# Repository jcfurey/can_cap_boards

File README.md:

# can_cap_boards

A repo to contain different PCBs with associated gerber files and SPICE sim docs.

The theme: small interior-mount boards that retire vintage multi-section
twist-lock "can" electrolytics in tube amps, replacing them with discrete,
individually serviceable modern radial caps.

> ⚠️ These boards carry **lethal B+ voltages** (400 V+). Discharge and meter
> every section to zero before handling. See each board's README.

## Boards

| Board | Amp | What it replaces | Status |
|-------|-----|------------------|--------|
| [`princeton_reverb_aa1164`](princeton_reverb_aa1164/) | Fender Princeton Reverb (AA1164) | 4-section can → 47/22/22/33 µF | design + BOM + SPICE + KiCad project (DRC-clean starter) + gerbers |

Each board folder contains its own `README.md` (design notes), `BOM.md`, an
illustrated `design_reference.html` (schematic + mechanical drawings), a `sim/`
directory with the SPICE supply model, and a `kicad/` directory with the KiCad
sources and `kicad/fab/` fabrication outputs (gerbers, drill, BOM, position).

## License

Apache-2.0 (see [`LICENSE`](LICENSE)).

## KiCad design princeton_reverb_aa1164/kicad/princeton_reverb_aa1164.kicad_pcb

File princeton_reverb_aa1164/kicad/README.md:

# KiCad project — AA1164 Filter Cap Board

KiCad 7 project for the Princeton Reverb (AA1164) filter-cap board. This is a
**starting point**: electrically complete, ERC/DRC-clean, with the HV creepage
and split-ground rules baked in — but the placement and mechanical fit still
want a pass in the GUI before you fab it.

> Built/validated with KiCad **7.0.11**. KiCad 9 opens it fine (it will offer to
> upgrade the files). The two generator scripts below are the scaffolding used
> to create it; the `.kicad_sch` / `.kicad_pcb` are now the editable sources.

*B.Cu split ground pours (blue) joined only at the NT1 star-tie; F.Cu B+ traces
(red); 2×2 caps with each B+ wire-entry beside its cap; bleeder R1/R2 top-left;
mounting holes right. The wide white rings are the 2.5 mm HV anti-pads in the
pour.*

## Files

| File | What |
|------|------|
| `princeton_reverb_aa1164.kicad_pro` | Project (net classes: 2.5 mm clearance / 2.5 mm tracks) |
| `princeton_reverb_aa1164.kicad_sch` | Schematic — 4 caps, bleeder, 6 wire-entry pads, star-tie, 2 mounts |
| `princeton_reverb_aa1164.kicad_pcb` | 2-layer board: B+ on F.Cu, split GND pours on B.Cu |
| `wire_entry.pretty/` | Custom footprints: `WireEntry_BPlus`, `WireEntry_GND` (1.6 mm hole / 3.3 mm pad), `StarTie_8mm` (net-tie) |
| `fp-lib-table` / `sym-lib-table` | Register the project footprint library |
| `generate_sch.py` / `generate_pcb.py` | The scripts that generated the above (kiutils + pcbnew) |
| `fab/` | Fabrication outputs — see `fab/` |
| `drc.rpt` | Saved DRC run (0 errors) |

## Nets & rules

- B+ nodes are **separate nets** `HV_A..HV_D` (each = wire-entry pad + cap "+",
  plus the bleeder on A) — they only join *outside* the board, in the amp.
- `BLEED_MID` is the junction of the two series bleeder resistors.
- Grounds are **two nets** `GND-PWR` (caps A·B + bleeder) and `GND-PRE`
  (caps C·D), joined **only** at the `NT1` star-tie (a net-tie footprint, so DRC
  permits the single intentional short). Omit/DNP NT1 to run dual returns.
- Board-wide clearance is **2.5 mm** and default track width **2.5 mm** — every
  net here is HV or ground, so one rule enforces the creepage spec everywhere.

## Validation

- **Connectivity** verified by netlist export (matches the intended net map).
- **DRC: 0 errors.** The 12 remaining items are warnings only:
  - `lib_footprint_issues` (8) — headless DRC has no global footprint-library
    table; these disappear in the GUI.
  - `silk_over_copper` (4) — cosmetic cap-outline silk over mask openings.
- KiCad 7's `kicad-cli` has no `erc`/`drc` subcommand (KiCad 8+), so ERC/DRC were
  run via the netlist export and `pcbnew.WriteDRCReport`. **Re-run ERC and DRC in
  your GUI** as a final check after any edits.

## Refine before fabbing

This was placed/routed *blind to the real chassis*. In the GUI:

1. **Verify mechanical fit** — board outline (~60 × 54 mm here vs the ~55–60 × 48
   target), the wire-entry positions against your fiber board, and cap body
   height clearance into the interior.
2. Optionally **regroup the wire-entry pads into one edge row** (they're placed
   next to each cap here for short, clean B+ traces).
3. Confirm the **cap footprints** — all four use `CP_Radial_D16.0mm_P7.50mm`
   (sized for the 47 µF); the 22/33 µF bodies are smaller, so swap to the right
   case once you pick exact parts.
4. Confirm the **bleeder** uses a vertical 2 W footprint that matches your
   resistors, and that the **star-tie** location suits your single chassis tie.
5. Re-run ERC + DRC.

## Regenerating

```sh
pip install kiutils
python3 generate_sch.py      # writes the .kicad_sch
python3 generate_pcb.py      # writes the .kicad_pcb, fills zones, runs DRC
```
Regenerating overwrites GUI edits — once you start editing in KiCad, treat the
`.kicad_sch`/`.kicad_pcb` as the sources and retire the scripts.

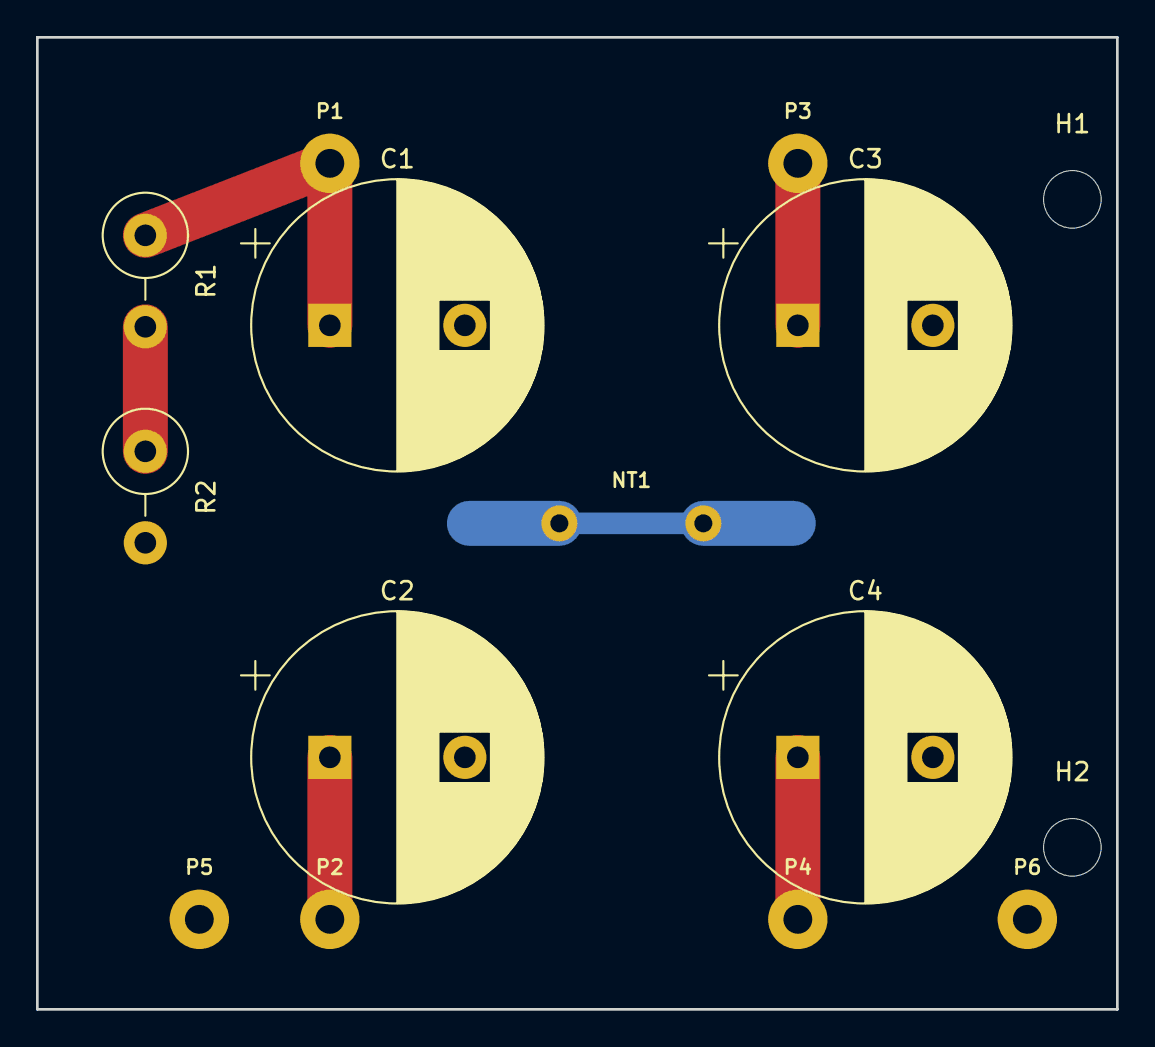
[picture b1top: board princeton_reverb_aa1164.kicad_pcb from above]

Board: 2 copper layers, 60.0 x 54.0 mm, 15 parts (0 on the bottom side), 7 nets.

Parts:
C1: 47uF; CP_Radial_D16.0mm_P7.50mm
C2, C3: 22uF; CP_Radial_D16.0mm_P7.50mm
C4: 33uF; CP_Radial_D16.0mm_P7.50mm
H1, H2: MountingHole_3.2mm_M3
NT1: STAR; StarTie_8mm
P1: B+1_A; WireEntry_BPlus
P2: B+2_B; WireEntry_BPlus
P3: B+3_C; WireEntry_BPlus
P4: B+4_D; WireEntry_BPlus
P5: GND-PWR; WireEntry_GND
P6: GND-PRE; WireEntry_GND
R1, R2: 100k; R_Axial_DIN0414_L11.9mm_D4.5mm_P5.08mm_Vertical

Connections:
BLEED_MID: R1.2, R2.1
GND-PRE: C3.2, C4.2, NT1.2, P6.1
GND-PWR: C1.2, C2.2, NT1.1, P5.1, R2.2
HV_A: C1.1, P1.1, R1.1
HV_B: C2.1, P2.1
HV_C: C3.1, P3.1
HV_D: C4.1, P4.1

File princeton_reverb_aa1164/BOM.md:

# BOM — Princeton Reverb (AA1164) Filter Cap Board

Rev F electrical design. Quantities are **per board**.

> **Scope:** only the parts that live *on this board* — the four filter caps,
> the bleeder, and the ground star link. The dropping resistors (1 k / 4.7 k /
> 10 k) between nodes stay on the amp's eyelet board and are **not** part of this
> BOM; they appear in the SPICE model (`sim/`) only to reproduce the node
> voltages.

## Filter capacitors

All electrolytics: aluminium, radial, **≥ 500 V**, **105 °C**, 7.5 mm pitch.
Anchor family: **Nichicon UCY** (voltage code `2H` = 500 V, `M` = ±20 %).
Confirm the exact case-size suffix at the distributor — it varies with µF.

| Ref | Node | Value | Rating | Suggested P/N | Qty |
|-----|------|------:|--------|---------------|:---:|
| C1 | A — B+1 reservoir / 6V6 plates | 47 µF | 500 V 105 °C | Nichicon UCY2H470MHD (16 × 40 mm) | 1 |
| C2 | B — B+2 screens | 22 µF | 500 V 105 °C | Nichicon UCY2H220M&lt;suffix&gt; | 1 |
| C3 | C — B+3 PI / reverb driver | 22 µF | 500 V 105 °C | Nichicon UCY2H220M&lt;suffix&gt; | 1 |
| C4 | D — B+4 preamp / reverb recovery | 33 µF | 500 V 105 °C | Nichicon UCY2H330M&lt;suffix&gt; | 1 |

- C1 bumped to 47 µF to firm the low end (stays under the GZ34's ~60 µF
  input-cap limit).
- C4 footprint laid out to accept **up to 47 µF** so node D stays retunable.
- 22 µF on C2/C3 is the stock value — more capacitance there buys nothing
  audible (confirmed by `sim/`: C/D ripple is already single-digit mV).

## Bleeder

| Ref | Value | Rating | Notes | Qty |
|-----|------:|--------|-------|:---:|
| R1, R2 | 100 kΩ | 2 W, ≥ 350 V | In series = 200 kΩ across node A → GND-PWR | 2 |

Metal-oxide / flameproof, axial. ~0.9 W total across node A, split (~0.45 W
each). Drains node A at power-off; downstream nodes drain through the amp's
dropping resistors while the board is connected. **Still meter every section to
zero before servicing.**

## Grounding / hardware

These are **board features**, not purchased parts (except the standoffs) —
listed so nothing is missed at layout.

| Ref | Item | Notes | Qty |
|-----|------|-------|:---:|
| P1–P4 | B+ wire-entry pads (PTH) | ~1.6 mm finished hole / ~3.3 mm pad, in a row on the fiber-board-facing edge; existing B+ wires poke up and solder in. | 4 |
| GND-PWR, GND-PRE | Ground wire-entry pads (PTH) + chassis lug | Separate dirty (A·B) and clean (C·D) returns; meet at the star. | 2 |
| JP1 | Star link (net-tie) | Joins GND-PWR ↔ GND-PRE at one point. Fit a wire/0 Ω link for single-point tie; omit to run dual returns to the amp's own buses. | 0–1 |
| — | Mounting standoffs + screws | Both mount holes isolated from copper (or make exactly one the ground tie) to avoid a ground loop. | 2 ea |

## Bare board

| Item | Spec |
|------|------|
| PCB | FR-4, 2-layer, 1.6 mm, 1 oz Cu, ~55–60 × 48 mm. Within JLCPCB & OSH Park 2-layer rules. |

---

*Part numbers are suggestions, not the only valid choice — any radial
electrolytic at ≥ 500 V / 105 °C in the right µF and a 7.5 mm pitch / ≤ 16 mm
diameter case will fit. Verify the case suffix and physical size against the
footprint before ordering.*

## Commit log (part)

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2026-06-23 first structure
